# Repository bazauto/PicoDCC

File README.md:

# PicoDCC

DCC command station firmware for the Raspberry Pi Pico 2 (RP2350). It generates the DCC track
signal in PIO, speaks a partial [DCC-EX](https://dcc-ex.com/) protocol to JMRI and other
throttles over UART, and drives a Waveshare ST7789T3 touchscreen through LVGL.

Part of a four-repo control stack for the Westgate Hollow model railway:
[layout-orchestration](https://github.com/bazauto/layout-orchestration) (backend and operator
UI), [layout-feedback](https://github.com/bazauto/layout-feedback) (MicroPython sensor nodes),
[esp-layout-controller](https://github.com/bazauto/esp-layout-controller) (touchscreen
throttle), and this — the command station that puts the signal on the rails.

## What works

Throttle, function and accessory commands; main and programming track signal generation on
separate PIO blocks; track power and overcurrent detection; emergency stop; the LCD UI and
diagnostic log; and flash-backed configuration.

**Command coverage is partial and some things that look implemented are not** — CV programming
is declarations without bodies, ACK detection does not exist despite having tunable parameters,
and `<D CONFIG>` / `<D CAL>` are unreachable. [`docs/README.md`](docs/README.md) carries the
authoritative current-state table and the known-gaps list. Read it before assuming a feature
works, and do not infer behaviour from the upstream DCC-EX documentation.

## Hardware

| | |
|---|---|
| Board | Raspberry Pi Pico 2 (RP2350), `PICO_BOARD=pico2` |
| Host link | UART0 on GP0/GP1, 115200 — this is the DCC-EX command channel |
| Main track | PIO signal GP17, enable GP18, fault LED GP16, current on ADC0/GP26 |
| Programming track | PIO signal GP20, enable GP21, fault LED GP19, current on ADC1/GP27 |
| Display | ST7789T3 over SPI0 (GP2–GP7), CST328 touch over I2C0 (GP8–GP11) |

Full pin map, including what is free for expansion, in
[`docs/gpio-pinout-reference.md`](docs/gpio-pinout-reference.md).

The carrier PCB — KiCad project, BOM and the Gerbers the boards were made from — is in
[`hardware/`](hardware/README.md), along with the concerns found in revision 1.0.

`printf()` goes to USB CDC, not the UART — USB output is for bring-up only, never the protocol
channel.

## Build

Two mutually exclusive modes, each with its own build tree, driven by `CMakePresets.json`.
Always go through a preset.

```bash
# host — host compiler + Ninja + CMocka. This is what you run for almost everything.
cmake --preset host
cmake --build --preset host
ctest --preset host                       # 11 suites, ~0.5s

# pico — ARM GCC cross-build, produces build/pico/src/PicoDCC.uf2
cmake --preset pico
cmake --build --preset pico
```

The hardware build needs `PICO_SDK_PATH` and `PICO_TOOLCHAIN_PATH`, and the **LVGL submodule**:

```bash
git submodule update --init --depth 1 lib/external/lvgl
```

CI runs the `host` preset on every push and PR. It does **not** cross-build firmware, so
hardware-mode breakage is not caught by CI — run the `pico` preset locally before merging
anything that touches shared headers or code behind `#ifdef TEST_BUILD`.

## Architecture

Work is split across both cores:

- **Core 0** parses DCC-EX commands off the UART, orchestrates, and owns the main command queue
  and the operation-mode state machine.
- **Core 1** drives the PIO state machines, monitors current via ADC, and generates locomotive
  reminders when the hardware queue empties. Reminders are hardware-paced, so the queue cannot
  overflow.

Priority is explicit commands > reminders > idle packets. The main track is the pacer and the
only track allowed to block; the programming track skips a pass rather than waiting.

Component responsibilities, the queue design and the operation modes are in
[`docs/architecture.md`](docs/architecture.md).

## Testing

Tests are CMocka, one suite per component, and two of them go further than unit testing:

- `test/pico_dcc_wire_format_tests.cpp` pins the **exact bytes** put on the rails and returned
  to the host. Some assertions deliberately record current *defective* behaviour and name the
  issue, so a fix shows up as a reviewable diff rather than a silent change.
- `test/pico_dcc_pio_tests.cpp` asserts on the **waveform**. It drives the real `sendCommand()`,
  runs the words it pushed through an emulator that executes the *assembled* `dcc.pio`, and
  decodes the result back into bits. That is what catches defects in the packing or the PIO
  timing, neither of which is visible from the packet buffers.

## Safety

This is firmware that puts current on rails, and two constraints are not negotiable.

**Flash writes block both cores for ~410ms.** DCC packets stop, and a decoder that loses the
signal falls back to DC mode — which on a powered track means full speed. Flash writes are
therefore only legal in Layout Maintenance Mode, which requires the main track to be unpowered
and can only be entered from the LCD. Physical presence, never remotely.

**The DCC-EX UART carries protocol replies only.** Errors, warnings and traces go to the
diagnostic log and the LCD. A stray diagnostic on the command UART desynchronises JMRI.

The full analysis is in
[`docs/safety-recommendations.md`](docs/safety-recommendations.md). Project rules, conventions
and workflow are in [`CLAUDE.md`](CLAUDE.md).

## Licence

The firmware is MIT — see [`LICENSE`](LICENSE). The carrier board design in `hardware/` is
CERN-OHL-P-2.0 — see [`hardware/LICENSE`](hardware/LICENSE). Third-party components, the scope
of each grant, and why
implementing DCC itself needs no licence are recorded in
[`THIRD_PARTY_NOTICES.md`](THIRD_PARTY_NOTICES.md).

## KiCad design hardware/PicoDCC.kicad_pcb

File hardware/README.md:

# PicoDCC carrier board

The carrier PCB the firmware runs on: a Raspberry Pi Pico 2 soldered down, two BTS7960 H-bridge
modules (main and programming track), their fault LEDs, and headers for the display and debug.
KiCad project, BOM and the Gerbers as sent to fab.

It was designed in KiCad 9.0.1 in April 2025, before this repo had any design review, and it is
imported as it was built. Nothing in the KiCad files has been changed on the way in. The concerns
found while importing it are listed [below](#known-concerns-with-revision-10) rather than fixed,
because the boards in use are this revision.

## Files

| File | What it is |
|---|---|
| `PicoDCC.kicad_pro`, `.kicad_sch`, `.kicad_pcb` | The KiCad project. Keep them together |
| `ProjectSymbols.kicad_sym` + `sym-lib-table` | The one project symbol, the BTS7960 module. Everything else comes from the stock KiCad libraries |
| `bom.csv` | Bill of materials, as exported from the schematic |
| `fab/rev-1.0/` | Gerbers, drill files, Gerber job file and the zipped set, as plotted on 2025-04-26 for the boards in use. A historical record: never regenerate it in place |
| `LICENSE` | CERN-OHL-P-2.0, covering everything in this folder |

The title block carries no revision, so "1.0" is a name given on import for the only revision
there has been. A board change that goes to fab gets a new `fab/rev-X.Y/` folder.

KiCad plots into `Gerber/` by default, which is git-ignored so that a fresh plot is never mistaken
for the fab record. Opening the project in KiCad 10 and saving it upgrades the file format;
do that deliberately, in its own commit.

## Connections

`A1` is the Pico 2. Pin numbers are the Pico's.

| Pico | Net | Goes to |
|---|---|---|
| GP0–GP15 | one net each | **J1** pins 1–16 (GP*n* on pin *n*+1). J1 carries the display, touch and UART, plus the spare GP12–GP15 |
| GP0, GP1 | UART0 | also **J2** pins 3, 4 |
| GP16 | main fault LED | D1 cathode; anode through R5 (330R) to GND — see concern 1 |
| GP17 | main DCC signal | U1 RPWM, TP1; inverted by Q1 (BC108, R1 base, R2 pull-up to VSYS) into U1 LPWM |
| GP18 | main enable | U1 R_EN and L_EN, TP2 |
| GP19 | prog fault LED | D2 cathode; anode through R6 (330R) to GND |
| GP20 | prog DCC signal | U2 RPWM, TP4; inverted by Q2 (R3, R4) into U2 LPWM |
| GP21 | prog enable | U2 R_EN and L_EN, TP5 |
| GP26 / ADC0 | main current | U1 R_IS and L_IS tied, TP3, R7 (1k) to GND |
| GP27 / ADC1 | prog current | U2 R_IS and L_IS tied, TP6, R8 (1k) to GND |
| SWCLK, SWDIO | debug | **J2** pins 6, 5 |
| VSYS | 5 V in | **J4** pin 2, J2 pin 2, TP7, U1/U2 VCC |
| GND | | J4 pin 1, J2 pin 1, TP8, U1/U2 GND |

Not connected: 3V3, 3V3_EN, RUN, VBUS, ADC_VREF, AGND, GP22, GP28.

**J2 (debug)**: 1 GND, 2 VSYS, 3 GP0, 4 GP1, 5 SWDIO, 6 SWCLK.
**J4 (power)**: 1 GND, 2 VSYS.

## Verification

Run on import with KiCad 10.0.5 (`kicad-cli`), against the files in this folder:

```
sch erc --severity-all                4 violations, all lib_symbol_mismatch (BC108 x2, LED_Small x2)
sch erc --severity-error              0
pcb drc --schematic-parity            0 unconnected items, 0 schematic parity issues
pcb drc, all severities               28: 27 lib_footprint_mismatch, 1 starved_thermal (error)
```

The mismatches are library drift: the design embeds the KiCad 9 copies of stock symbols and
footprints, and KiCad 10's libraries have moved on. They are not connection problems. The
starved thermal is concern 4.

The schematic was last saved in August 2025, four months after the board. The zero parity result
shows the board still matches it.

`fab/rev-1.0/` was checked against the board by replotting the Gerbers and drill files with
`kicad-cli` and comparing what each file draws, using the geometry comparison from
`bazauto/block-detection`'s `scripts/check_fab_outputs.py`. All 12 files match. The only textual
difference is that KiCad 10 numbers the three custom pad-shape aperture macros in a different
order from 9.0.1.

## Known concerns with revision 1.0

**1. The fault LEDs are drawn reverse-biased.** GP16 drives D1's cathode and the anode returns
to GND through R5, so driving GP16 high — what the firmware does on a trip — reverse-biases the
LED. D2 on GP19 is the same. Check how the LEDs were actually fitted before relying on them: if
they light, they are in the other way round from the footprint.

**2. 3V3 is not broken out.** J1 carries GP0–GP15 only; neither J1 nor J2 has a 3V3 pin. Anything
that needs a 3.3 V supply from the board — the block detector used for programming-track ACK, for
one — has to take it from the Pico's 3V3 pin (pin 36) directly.

**3. Current sense resolution, and a possible overvoltage on the ADC pins.** The BTS7960's IS
output is a current proportional to load, at a ratio of roughly 8500:1, turned into a voltage by
the 1k to ground. At that ratio 60 mA — a decoder's service-mode ACK — is about 7 µA, about 7 mV,
about 9 ADC counts, which is below the sense offset the part is specified with at low current.
That is why ADC-based ACK detection never worked, and why ACK detection is moving to the block
detector. Separately, the BTS7960 datasheet describes the IS pin sourcing a fixed current of a few
milliamps when the chip latches a fault; if that is ~4.5 mA, 1k turns it into ~4.5 V on GP26/GP27,
and the RP2350's ADC-capable pins are not 5 V tolerant. **Unverified** — check the datasheet
figure before relying on the ADC pins surviving a driver fault.

**4. One starved thermal relief.** J2 pin 1 (GND) connects to the B.Cu ground zone with one
spoke where the zone asks for two. Harmless electrically; worth fixing in any next revision.

## Licence

Copyright © 2025–2026 Paul Barrett.

The design in this folder — schematic, board, project symbol library, BOM, Gerbers and drill
files — is licensed under the **CERN Open Hardware Licence Version 2 – Permissive**
([`LICENSE`](LICENSE)), the same licence as `bazauto/block-detection`. The firmware in the rest
of the repository stays MIT.

Symbols and footprints from the stock KiCad libraries are embedded in the schematic and board,
as KiCad always does. The KiCad libraries are CC-BY-SA 4.0 with an exception that a design using
them is not bound by that licence, so this folder carries no obligation from them. 3D models are
referenced by path, not included. See [`THIRD_PARTY_NOTICES.md`](../THIRD_PARTY_NOTICES.md).

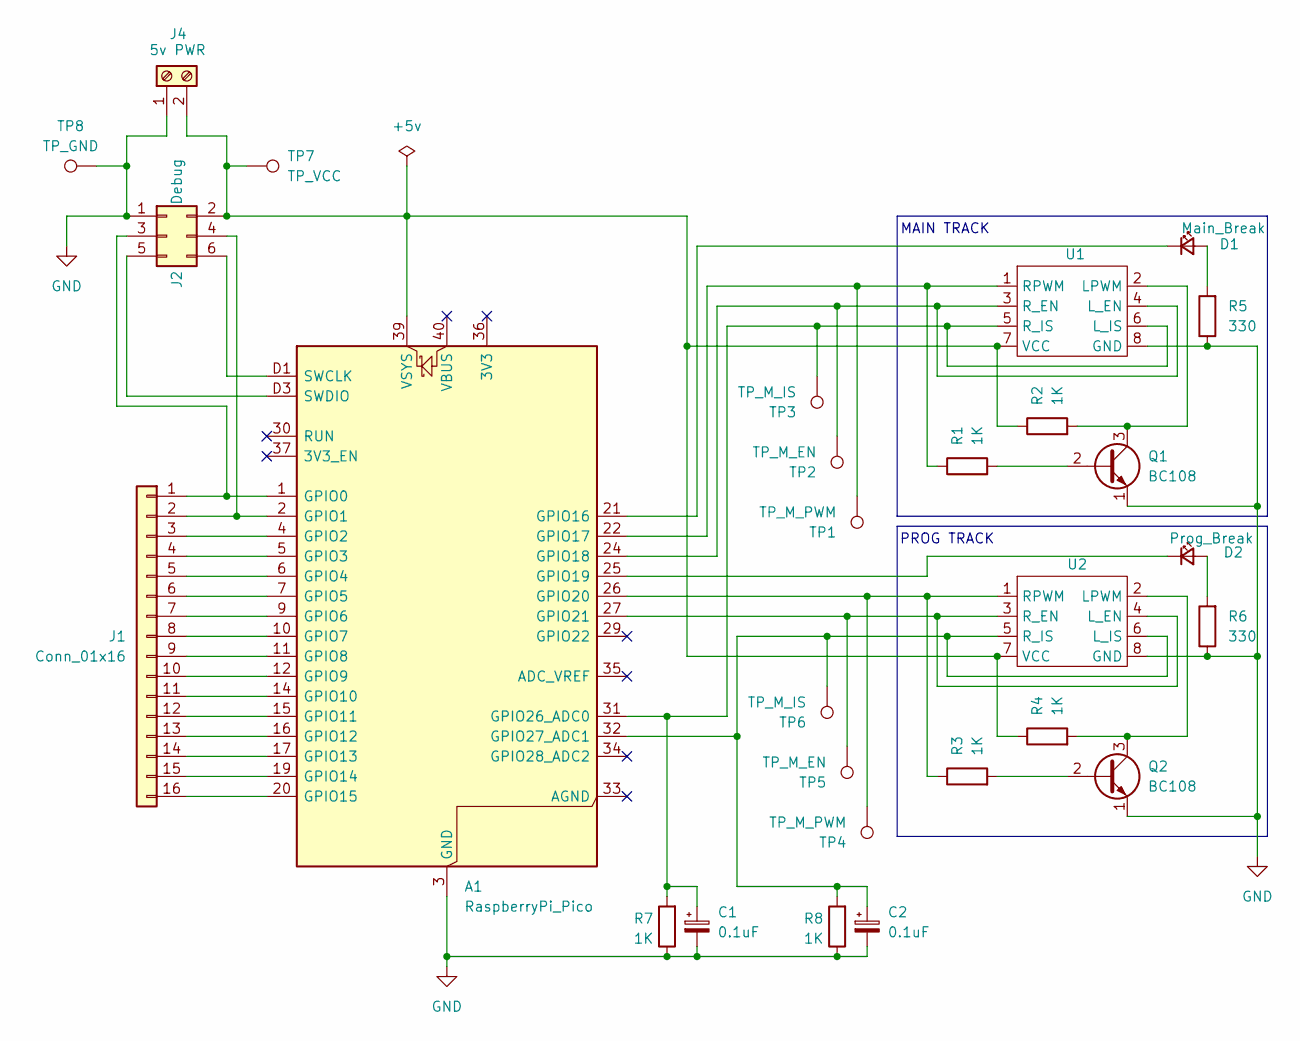
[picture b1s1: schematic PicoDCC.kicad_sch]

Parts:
A1: RaspberryPi_Pico; RaspberryPi_Pico_SMD_HandSolder
C1, C2: 0.1uF; CP_Radial_D4.0mm_P2.00mm
D1: Main_Break; LED_D3.0mm_Clear
D2: Prog_Break; LED_D3.0mm_Clear
J1: Conn_01x16; PinHeader_1x16_P2.54mm_Vertical
J2: Debug; PinHeader_2x03_P2.54mm_Vertical
J4: 5v PWR; TerminalBlock_RND_205-00012_1x02_P5.00mm_Horizontal
Q1, Q2: BC108; TO-18-3
R1, R2, R3, R4, R7, R8: 1K; R_Axial_DIN0207_L6.3mm_D2.5mm_P10.16mm_Horizontal
R5, R6: 330; R_Axial_DIN0207_L6.3mm_D2.5mm_P10.16mm_Horizontal
TP1, TP4: TP_M_PWM; PinSocket_1x01_P2.54mm_Vertical
TP2, TP5: TP_M_EN; PinSocket_1x01_P2.54mm_Vertical
TP3, TP6: TP_M_IS; PinSocket_1x01_P2.54mm_Vertical
TP7: TP_VCC; PinSocket_1x01_P2.54mm_Vertical
TP8: TP_GND; PinSocket_1x01_P2.54mm_Vertical
U1, U2: PinHeader_2x04_P2.54mm_Vertical

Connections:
GND: A1.3 (GND), A1.8 (GND), A1.13 (GND), A1.18 (GND), A1.23 (GND), A1.28 (GND), A1.38 (GND), A1.D2 (GND), C1.2, C2.2, J2.1, J4.1, Q1.1 (E), Q2.1 (E), R5.1, R6.1, R7.1, R8.1, TP8.1, U1.8 (GND), U2.8 (GND)
unnamed: A1.1 (GPIO0), J1.1, J2.3
unnamed: A1.2 (GPIO1), J1.2, J2.4
unnamed: A1.4 (GPIO2), J1.3
unnamed: A1.5 (GPIO3), J1.4
unnamed: A1.6 (GPIO4), J1.5
unnamed: A1.7 (GPIO5), J1.6
unnamed: A1.9 (GPIO6), J1.7
unnamed: A1.10 (GPIO7), J1.8
unnamed: A1.11 (GPIO8), J1.9
unnamed: A1.12 (GPIO9), J1.10
unnamed: A1.14 (GPIO10), J1.11
unnamed: A1.15 (GPIO11), J1.12
unnamed: A1.16 (GPIO12), J1.13
unnamed: A1.17 (GPIO13), J1.14
unnamed: A1.19 (GPIO14), J1.15
unnamed: A1.20 (GPIO15), J1.16
unnamed: A1.21 (GPIO16), D1.1 (K)
unnamed: A1.22 (GPIO17), R1.1, TP1.1, U1.1 (RPWM)
unnamed: A1.24 (GPIO18), TP2.1, U1.3 (R_EN), U1.4 (L_EN)
unnamed: A1.25 (GPIO19), D2.1 (K)
unnamed: A1.26 (GPIO20), R3.1, TP4.1, U2.1 (RPWM)
unnamed: A1.27 (GPIO21), TP5.1, U2.3 (R_EN), U2.4 (L_EN)
unnamed: A1.31 (GPIO26_ADC0), C1.1, R7.2, TP3.1, U1.5 (R_IS), U1.6 (L_IS)
unnamed: A1.32 (GPIO27_ADC1), C2.1, R8.2, TP6.1, U2.5 (R_IS), U2.6 (L_IS)
unnamed: A1.D1 (SWCLK), J2.6
unnamed: A1.D3 (SWDIO), J2.5
unnamed: A1.39 (VSYS), J2.2, J4.2, R2.1, R4.1, TP7.1, U1.7 (VCC), U2.7 (VCC)
unnamed: D1.2 (A), R5.2
unnamed: D2.2 (A), R6.2
unnamed: Q1.2 (B), R1.2
unnamed: Q1.3 (C), R2.2, U1.2 (LPWM)
unnamed: Q2.2 (B), R3.2
unnamed: Q2.3 (C), R4.2, U2.2 (LPWM)

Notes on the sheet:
PROG TRACK
MAIN TRACK

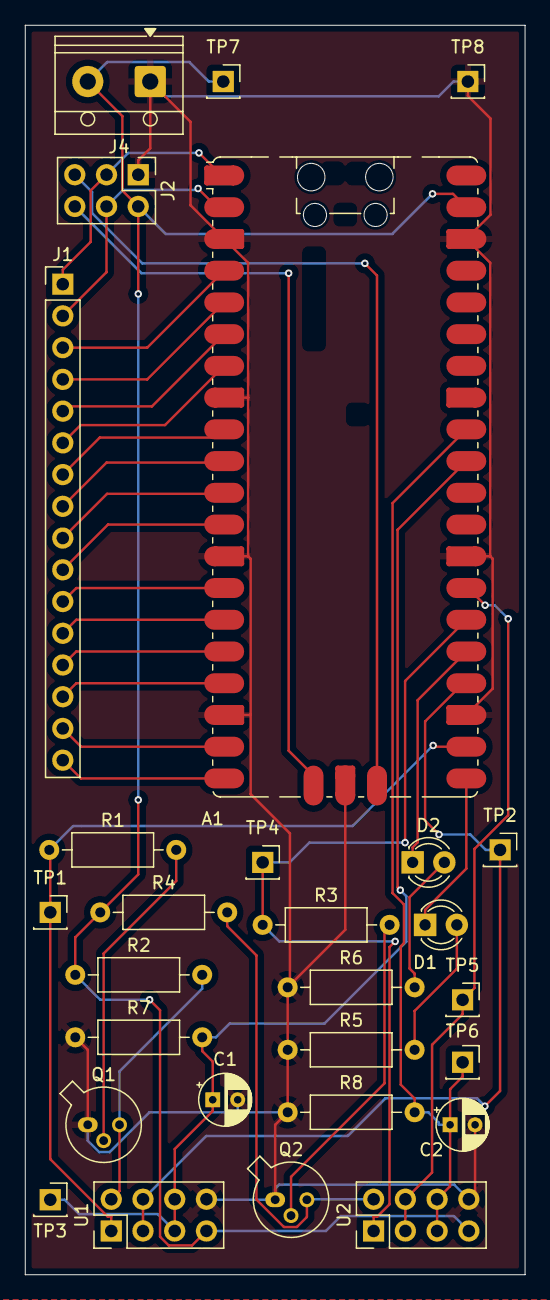
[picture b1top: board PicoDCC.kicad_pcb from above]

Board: 2 copper layers, 40.0 x 100.0 mm, 28 parts (0 on the bottom side), 34 nets.

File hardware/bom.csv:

"Reference","Value","Footprint","Datasheet","Qty","DNP","Exclude from BOM","Exclude from Board"
"A1","RaspberryPi_Pico","Module:RaspberryPi_Pico_SMD_HandSolder","https://datasheets.raspberrypi.com/pico/pico-datasheet.pdf","1","","",""
"C1,C2","0.1uF","Capacitor_THT:CP_Radial_D4.0mm_P2.00mm","~","2","","",""
"D1","Main_Break","LED_THT:LED_D3.0mm_Clear","~","1","","",""
"D2","Prog_Break","LED_THT:LED_D3.0mm_Clear","~","1","","",""
"J1","Conn_01x16","Connector_PinHeader_2.54mm:PinHeader_1x16_P2.54mm_Vertical","~","1","","",""
"J2","Debug","Connector_PinHeader_2.54mm:PinHeader_2x03_P2.54mm_Vertical","~","1","","",""
"J4","5v PWR","TerminalBlock_RND:TerminalBlock_RND_205-00012_1x02_P5.00mm_Horizontal","~","1","","",""
"Q1,Q2","BC108","Package_TO_SOT_THT:TO-18-3","http://www.b-kainka.de/Daten/Transistor/BC108.pdf","2","","",""
"R1,R2,R3,R4,R7,R8","1K","Resistor_THT:R_Axial_DIN0207_L6.3mm_D2.5mm_P10.16mm_Horizontal","~","6","","",""
"R5,R6","330","Resistor_THT:R_Axial_DIN0207_L6.3mm_D2.5mm_P10.16mm_Horizontal","~","2","","",""
"TP1,TP4","TP_M_PWM","Connector_PinSocket_2.54mm:PinSocket_1x01_P2.54mm_Vertical","~","2","","",""
"TP2,TP5","TP_M_EN","Connector_PinSocket_2.54mm:PinSocket_1x01_P2.54mm_Vertical","~","2","","",""
"TP3,TP6","TP_M_IS","Connector_PinSocket_2.54mm:PinSocket_1x01_P2.54mm_Vertical","~","2","","",""
"TP7","TP_VCC","Connector_PinSocket_2.54mm:PinSocket_1x01_P2.54mm_Vertical","~","1","","",""
"TP8","TP_GND","Connector_PinSocket_2.54mm:PinSocket_1x01_P2.54mm_Vertical","~","1","","",""
"U1,U2","~","Connector_PinHeader_2.54mm:PinHeader_2x04_P2.54mm_Vertical","","2","","",""

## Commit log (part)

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2024-06-20 Start of big refactoring
2024-06-22 Further refactoring
2024-06-25 Start adding in the Locos class to deal with the remembered list of locos
2025-01-11 First round of debugging and tweaks
2025-01-11 Refactor to push only data through the queue
2025-01-12 Finish more of the track processing and add setting for track signal pin as was hardcoded
2025-01-12 Try a different method to get the next loco to remind
2025-01-12 More debug
2025-01-13 Rework constructors to properly initialise the values
2025-01-16 Refactor DCC command process and add initial support for accessories
2025-01-26 Initial breaker code
2025-01-28 Debug session, fixes to get wifi throttle working
2025-01-29 First pass at adding uinit test framework
2025-02-02 Trying to add code coverage
2025-09-12 Got the tests compiling and running now
2025-10-08 Large refactor to minimise the work done by core 1 and hopefully improve stability.
    - Add DCC types, validation script, and comprehensive tests for PicoDCC
    - Created dcc_types.h to define raw DCC command structure.
    - Added Validate-DualMode.ps1 script for validating build modes and running tests.
    - Implemented test framework for PicoDCC controller and track functionalities.
    - Developed tests for command processing, power control, emergency stop, and idle packet generation.
    - Established global test variables for managing state across tests.
2025-10-08 Remove some extra files / folders that are no longer needed
2025-10-16 Add comprehensive safety recommendations and race condition analysis for PicoDCC system
2025-10-16 Implement core health monitoring and emergency power cutoff mechanism
2025-10-16 Update architecture documentation to include error handling and diagnostics details
2025-10-16 Enhance DCCEX packet validation and logging, improve type consistency in loco count, and suppress MSVC warnings for cross-platform compatibility
2025-10-16 Refactor CMakeLists.txt to streamline project definition for test build and suppress GCC ABI compatibility warnings
2025-10-16 Refactor DCCEX response handling for consistent UART communication in test and hardware modes
2025-10-18 Refactor locomotive reminder generation to Core 1 for improved queue management and overflow prevention
2025-10-18 Enhance command handling in DCC loops by adjusting repeat logic and routing inter-core commands to the appropriate track queues
2025-10-19 Add LCD integration analysis for Waveshare 2.7" touchscreen, including hardware specifications, integration architecture, and development recommendations.
2025-10-19 LCD Phase 1 Changes - ready for initial hardware test
    Implement LCD display integration with LVGL support, including driver and UI components
2025-10-19 Fix display update mechanism by forcing screen redraw and processing LVGL timers
2025-10-19 Update project descriptions and implement landscape orientation for LCD display
2025-10-19 Missed the doc update
2025-10-19 LCD Phase 4 - Initial Touchscreen Implement touch input support for Phase 4 with CST328 controller and interactive buttons
2025-10-19 Fix touch callback implementation for CST328 polling
    - Read touch data before checking state to avoid stale data
    - Scale 12-bit coordinates to screen resolution
    - Clear touch state properly when no touch is detected
    - Added debug output for first touch event to verify coordinate scaling
2025-10-19 Enhance touch handling with debug logging in callback and interrupt handler
2025-10-19 Add debug logging for update and touch callback functions
2025-10-19 Add debug logging for touch input registration and read timer status
2025-10-19 Add debug logging for touch read timer configuration and remove timing checks
2025-10-19 Add debug logging for touch callback and readTouchPoints function
2025-10-19 feat(lcd): Working touch calibration system with CST328
    - Fixed CST328 driver to use correct 16-bit register addresses (0xD000)
    - Fixed data format parsing (state field + proper coordinate extraction)
    - Added TouchCalibration class for 9-point calibration
    - Added serial command '<C>' to trigger calibration
    - Touch coordinates now map correctly with piecewise linear interpolation
    - Buttons respond correctly to touch input
2025-10-19 refactor(lcd): Simplify touch to essential coordinate transform
    Removed calibration system (600+ lines) in favor of simple linear mapping.
    The corrected CST328 driver provides clean coordinates that only need
    axis swap and inversion - no complex piecewise interpolation needed.
    Changes:
    - Replaced piecewise calibration with 10-line linear formula in touchCallback()
    - Removed TouchCalibration class (touch_calibration.cpp/h)
2025-10-19 docs(lcd): Consolidate LCD documentation into single file
    Replaced 13 separate LCD documentation files (~210KB total) with a single
    comprehensive lcd-integration.md (8.6KB). The new document covers:
    - Hardware configuration (pins, specs, memory)
    - Software architecture (LVGL, component structure)
    - Implementation status (Phases 1-4 complete)
    - Phase 5 planning (blocked on PicoConfigStorage)
2025-10-20 Fix test mode build issue
2025-10-20 feat: Implement diagnostic log display feature with circular buffer
    - Added diagnostic log storage infrastructure in pico_diagnostic.h and pico_diagnostic.cpp.
    - Implemented circular buffer for storing diagnostic messages with a maximum of 30 entries.
    - Created functions for initializing, adding, retrieving, and clearing log entries.
    - Developed LVGL UI for displaying logs, including navigation and color-coded severity levels.
    - Integrated log display into the main diagnostic screen with a log count indicator.
    - Added unit tests for log buffer operations, including initialization, addition, wrap-around, and clearing.
2025-10-20 Fix test mode compatibility: Add time_us_32() mock and fix diagnostic test string assignments
2025-10-20 Update DCC-EX compliance analysis: Revise CV programming status, enhance JMRI compatibility, and document implemented commands
2025-10-20 feat: Implement Layout Maintenance Mode state machine and hybrid config
    Core Components Implemented:
    - OperationMode enum (NORMAL, LAYOUT_MAINTENANCE) in PicoDCCController
    - Mode management: canEnterMaintenanceMode(), enterMaintenanceMode(), exitMaintenanceMode()
    - Main track power lockout enforcement in maintenance mode
    - Silent rejection of throttle/function/accessory commands during maintenance
    - Configuration access via getConfigStorage()
2025-10-20 feat: Add DCC-EX commands for runtime config and maintenance mode
    Commands Implemented:
    - <D ACK LIMIT mA> - Set ACK detection threshold (runtime, immediate effect)
    - <D ACK MIN us> - Set minimum ACK pulse duration (runtime)
    - <D ACK MAX us> - Set maximum ACK pulse duration (runtime)
    - <E> - Save configuration to flash (maintenance mode only, 410ms blocking)
    - <s> - Enhanced status with mode, unsaved changes, ACK config
2025-10-20 docs: Update JMRI compatibility notes with testing feedback
    Real-world JMRI Testing Results (October 20, 2025):
    - Random text: Silently ignored (no log entry)
    - <U ...>: Shows as unrecognized command in log (debug use)
    - <X>: Correctly interpreted as operation failed
    - Protocol extensions: Require Java driver fork (not viable)
    Documentation Updates:
2025-10-20 docs: Update config storage doc with completed Phase 3 (LCD UI)
    Marked Layout Maintenance Mode as complete:
    - Phase 1: Core state machine
    - Phase 2: DCC-EX commands
    - Phase 3: LCD Display UI
    Added detailed implementation notes for Phase 3 including:
    - 7 modified files
2025-10-20 Add unit tests for Layout Maintenance Mode
    Added 4 new controller tests (13 13 total, +4 MM tests):
    - test_maintenance_mode_entry_requirements: Entry validation
    - test_maintenance_mode_power_lockout: Main track power enforcement
    - test_maintenance_mode_command_rejection: Throttle/function/accessory rejection
    - test_maintenance_mode_exit: Mode exit and restore normal operation
    All tests passing with GCC/Ninja build configuration.
2025-10-20 Add gcov code coverage analysis tools and report
    - Add Generate-Coverage-Report.ps1 for automated coverage analysis
    - Generate comprehensive coverage report (64.96% overall)
    - Document Layout Maintenance Mode coverage (70% controller coverage)
    - Identify coverage gaps (PicoConfigStorage 28%, needs improvement)
    - All test suites passing with coverage instrumentation
2025-10-20 Implement hardware testing quick reference and custom linker script for configuration preservation
    - Added a comprehensive hardware testing quick reference card detailing features, tests, equipment, commands, safety checklist, firmware update procedures, and expected timing.
    - Created a custom linker script (`memmap_picodcc.ld`) to reserve the last 4KB of flash for configuration storage, ensuring firmware updates do not erase critical settings.
    - Updated documentation to reflect the new automatic configuration preservation during firmware updates, reducing manual backup/restore steps.
    - Verified build status and firmware size analysis to ensure compliance with the new memory layout.
    - Enhanc
2025-10-21 Update PicoDCC configuration handling and display improvements
    - Adjusted flash storage offset for 4MB flash configuration.
    - Enhanced PicoDccController to handle configuration commands more efficiently, including ACK LIMIT, ACK MIN, and ACK MAX commands.
    - Updated PicoDccExPacket to parse and validate configuration commands with appropriate ranges.
    - Added unit tests for configuration commands to ensure correct parsing and validation.
    - Improved the display modal for maintenance mode entry, making it non-blocking and enhancing button responsiveness.
    - Removed deprecated pico_dcc_display.cpp file and refactored related display logic.
2025-10-21 Add PicoDCC Programmer for CV Operations and Unit Tests
    - Implemented PicoDccProgrammer class for handling CV read/write operations on the programming track using NMRA Direct Mode packets.
    - Added methods for ACK detection, baseline current measurement, and CV read workflows.
    - Defined constants for ACK detection parameters and CV addressing.
    - Created unit tests for the PicoDccProgrammer, covering constructor behavior, configuration loading, baseline current measurement, ACK detection, packet generation, and CV read operations.
    - Ensured tests validate expected behavior through a test-driven development approach.
2025-11-30 Enhance LVGL Renderer and Track Management
    - Updated LVGL renderer to include new theme color definitions for better UI consistency.
    - Refactored diagnostic screen to improve layout and button functionality, including power state indicators for main and programming tracks.
    - Added support for track tripping state in the TrackStatus structure and updated related logic in the PicoDccTrack class.
    - Removed unnecessary test pattern display during boot sequence for a more streamlined startup experience.
    - Improved button event handling for power toggling, ensuring correct state management and feedback.
    - Updated log and locomotive count displays to limit to two digits for consistency.
